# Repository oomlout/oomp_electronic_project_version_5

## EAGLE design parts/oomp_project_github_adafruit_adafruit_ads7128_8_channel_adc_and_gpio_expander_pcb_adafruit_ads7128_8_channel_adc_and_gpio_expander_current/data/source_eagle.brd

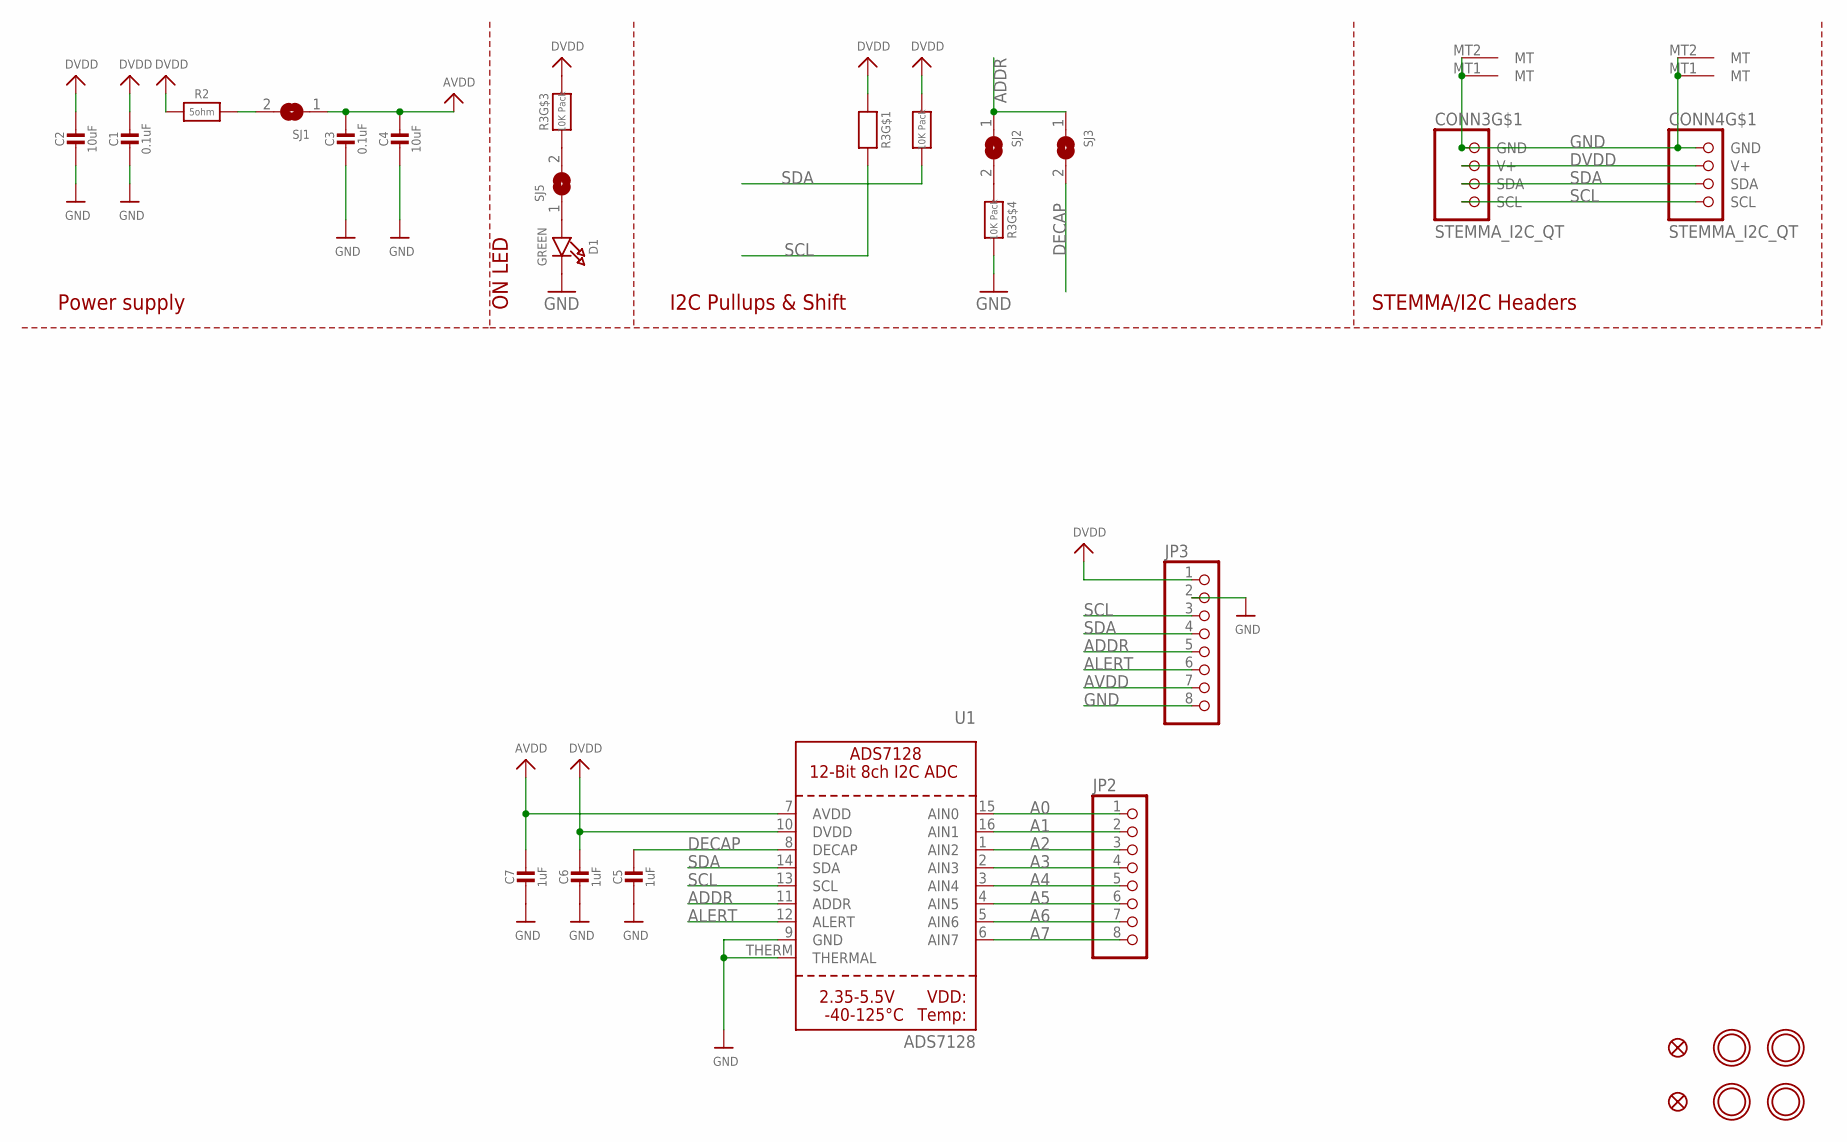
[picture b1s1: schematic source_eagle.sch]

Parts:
C1, C3: 0.1uF; 0603-NO
C2, C4: 10uF; 0805-NO
C5, C6, C7: 1uF; 0603-NO
CONN3, CONN4: STEMMA_I2C_QT; JST_SH4
D1: GREEN; CHIPLED_0603_NOOUTLINE
FID3, FID4: FIDUCIAL_0.5MM
JP2, JP3: HEADER-1X870MIL; 1X08_ROUND_70
R2: 5ohm; 0603-NO
R3: 10K Pack; RESPACK_4X0603
SJ1, SJ5: SOLDERJUMPERCLOSED; SOLDERJUMPER_CLOSEDWIRE
SJ2, SJ3: SOLDERJUMPER; SOLDERJUMPER_ARROW_NOPASTE
U1: ADS7128; WQFN16
U$1, U$17, U$19, U$21: MOUNTINGHOLE2.5; MOUNTINGHOLE_2.5_PLATED

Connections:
A0: JP2.1, U1.15 (AIN0)
A1: JP2.2, U1.16 (AIN1)
A2: JP2.3, U1.1 (AIN2)
A3: JP2.4, U1.2 (AIN3)
A4: JP2.5, U1.3 (AIN4)
A5: JP2.6, U1.4 (AIN5)
A6: JP2.7, U1.5 (AIN6)
A7: JP2.8, U1.6 (AIN7)
ADDR: JP3.5, SJ2.1, SJ3.1, U1.11 (ADDR)
ALERT: JP3.6, U1.12 (ALERT)
AVDD: C3.1, C4.1, C7.1, JP3.7, SJ1.1, U1.7 (AVDD)
DECAP: C5.1, SJ3.2, U1.8 (DECAP)
DVDD: C1.1, C2.1, C6.1, CONN3.2 (V+), CONN4.2 (V+), JP3.1, R2.1, R3.1, R3.2 (1), R3.6 (2), U1.10 (DVDD)
GND: C1.2, C2.2, C3.2, C4.2, C5.2, C6.2, C7.2, CONN3.1 (GND), CONN3.MT1 (MT), CONN3.MT2 (MT), CONN4.1 (GND), CONN4.MT1 (MT), CONN4.MT2 (MT), D1.C, JP3.2, JP3.8, R3.5 (2), U1.9 (GND), U1.THERM (THERMAL)
unnamed: D1.A, SJ5.1
unnamed: R3.3 (1), SJ5.2
unnamed: R2.2, SJ1.2
unnamed: R3.4 (1), SJ2.2
SCL: CONN3.4 (SCL), CONN4.4 (SCL), JP3.3, R3.8 (2), U1.13 (SCL)
SDA: CONN3.3 (SDA), CONN4.3 (SDA), JP3.4, R3.7 (2), U1.14 (SDA)

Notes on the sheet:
I2C Pullups & Shift
STEMMA/I2C Headers
ON LED
Power supply

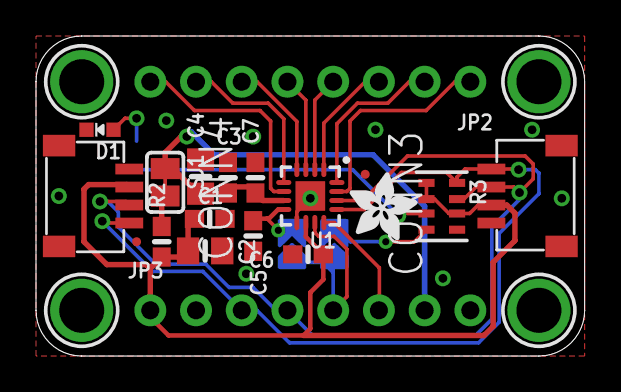
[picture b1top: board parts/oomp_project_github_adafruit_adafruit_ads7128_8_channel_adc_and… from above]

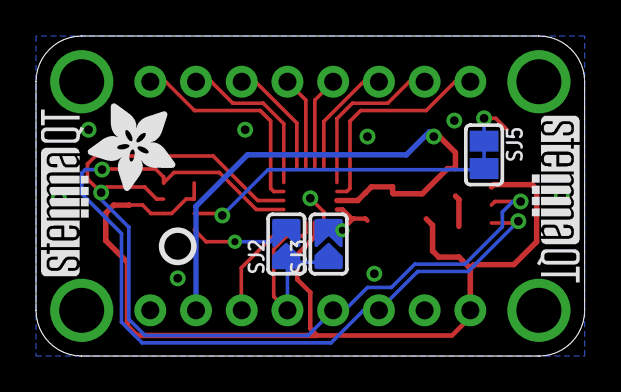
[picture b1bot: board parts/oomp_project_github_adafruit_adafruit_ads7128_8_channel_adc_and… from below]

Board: 2 copper layers, 30.5 x 17.8 mm, 58 parts (14 on the bottom side), 20 nets.

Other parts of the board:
PLABEL0: PLABEL0
PLABEL2: PLABEL2
PLABEL3: PLABEL3
PLABEL4: PLABEL4
PLABEL7: PLABEL7
PLABEL10: PLABEL10
PLABEL11: PLABEL11
PLABEL12: PLABEL12
PLABEL13: PLABEL13
PLABEL14: PLABEL14
PLABEL15: PLABEL15
PLABEL16: PLABEL16
PLABEL17: PLABEL17
PLABEL20: PLABEL20
PLABEL25: PLABEL25
PLABEL26: PLABEL26
PLABEL27: PLABEL27
PLABEL28: PLABEL28
PLABEL29: PLABEL29
PLABEL30: PLABEL30
PLABEL31: PLABEL31
PLABEL32: PLABEL32
PLABEL33: PLABEL33
PLABEL34: PLABEL34
PLABEL35: PLABEL35
PLABEL36: PLABEL36
PLABEL37: PLABEL37
PLABEL38: PLABEL38
U$22: ADAFRUIT_3.5MM
U$25: PCBFEAT-REV-040
U$27: ADAFRUIT_5MM
U$30, U$31: STEMMAQT

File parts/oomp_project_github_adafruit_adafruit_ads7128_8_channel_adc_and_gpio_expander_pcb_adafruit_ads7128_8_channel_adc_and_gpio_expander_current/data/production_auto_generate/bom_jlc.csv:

Comment,Designator,Footprint,LCSC Part #
,"JP2,JP3",1X08_ROUND_70,C492421
,U$22,ADAFRUIT_3.5MM,
,U$27,ADAFRUIT_5MM,
,U$25,PCBFEAT-REV-040,
,PLABEL0,PLABEL0,
,PLABEL10,PLABEL10,
,PLABEL11,PLABEL11,
,PLABEL12,PLABEL12,
,PLABEL13,PLABEL13,
,PLABEL14,PLABEL14,
,PLABEL15,PLABEL15,
,PLABEL16,PLABEL16,
,PLABEL17,PLABEL17,
,PLABEL2,PLABEL2,
,PLABEL20,PLABEL20,
,PLABEL25,PLABEL25,
,PLABEL26,PLABEL26,
,PLABEL27,PLABEL27,
,PLABEL28,PLABEL28,
,PLABEL29,PLABEL29,
,PLABEL3,PLABEL3,
,PLABEL30,PLABEL30,
,PLABEL31,PLABEL31,
,PLABEL32,PLABEL32,
,PLABEL33,PLABEL33,
,PLABEL34,PLABEL34,
,PLABEL35,PLABEL35,
,PLABEL36,PLABEL36,
,PLABEL37,PLABEL37,
,PLABEL38,PLABEL38,
,PLABEL4,PLABEL4,
,PLABEL7,PLABEL7,
,"U$30,U$31",STEMMAQT,
0.1uF,"C1,C3",0603-NO,C14663
10K Pack,R3,RESPACK_4X0603,C98220
10uF,"C2,C4",0805-NO,
1uF,"C5,C6,C7",0603-NO,C5673
5ohm,R2,0603-NO,
ADS7128,U1,WQFN16,
GREEN,D1,CHIPLED_0603_NOOUTLINE,
STEMMA_I2C_QT,"CONN3,CONN4",JST_SH4,C160404

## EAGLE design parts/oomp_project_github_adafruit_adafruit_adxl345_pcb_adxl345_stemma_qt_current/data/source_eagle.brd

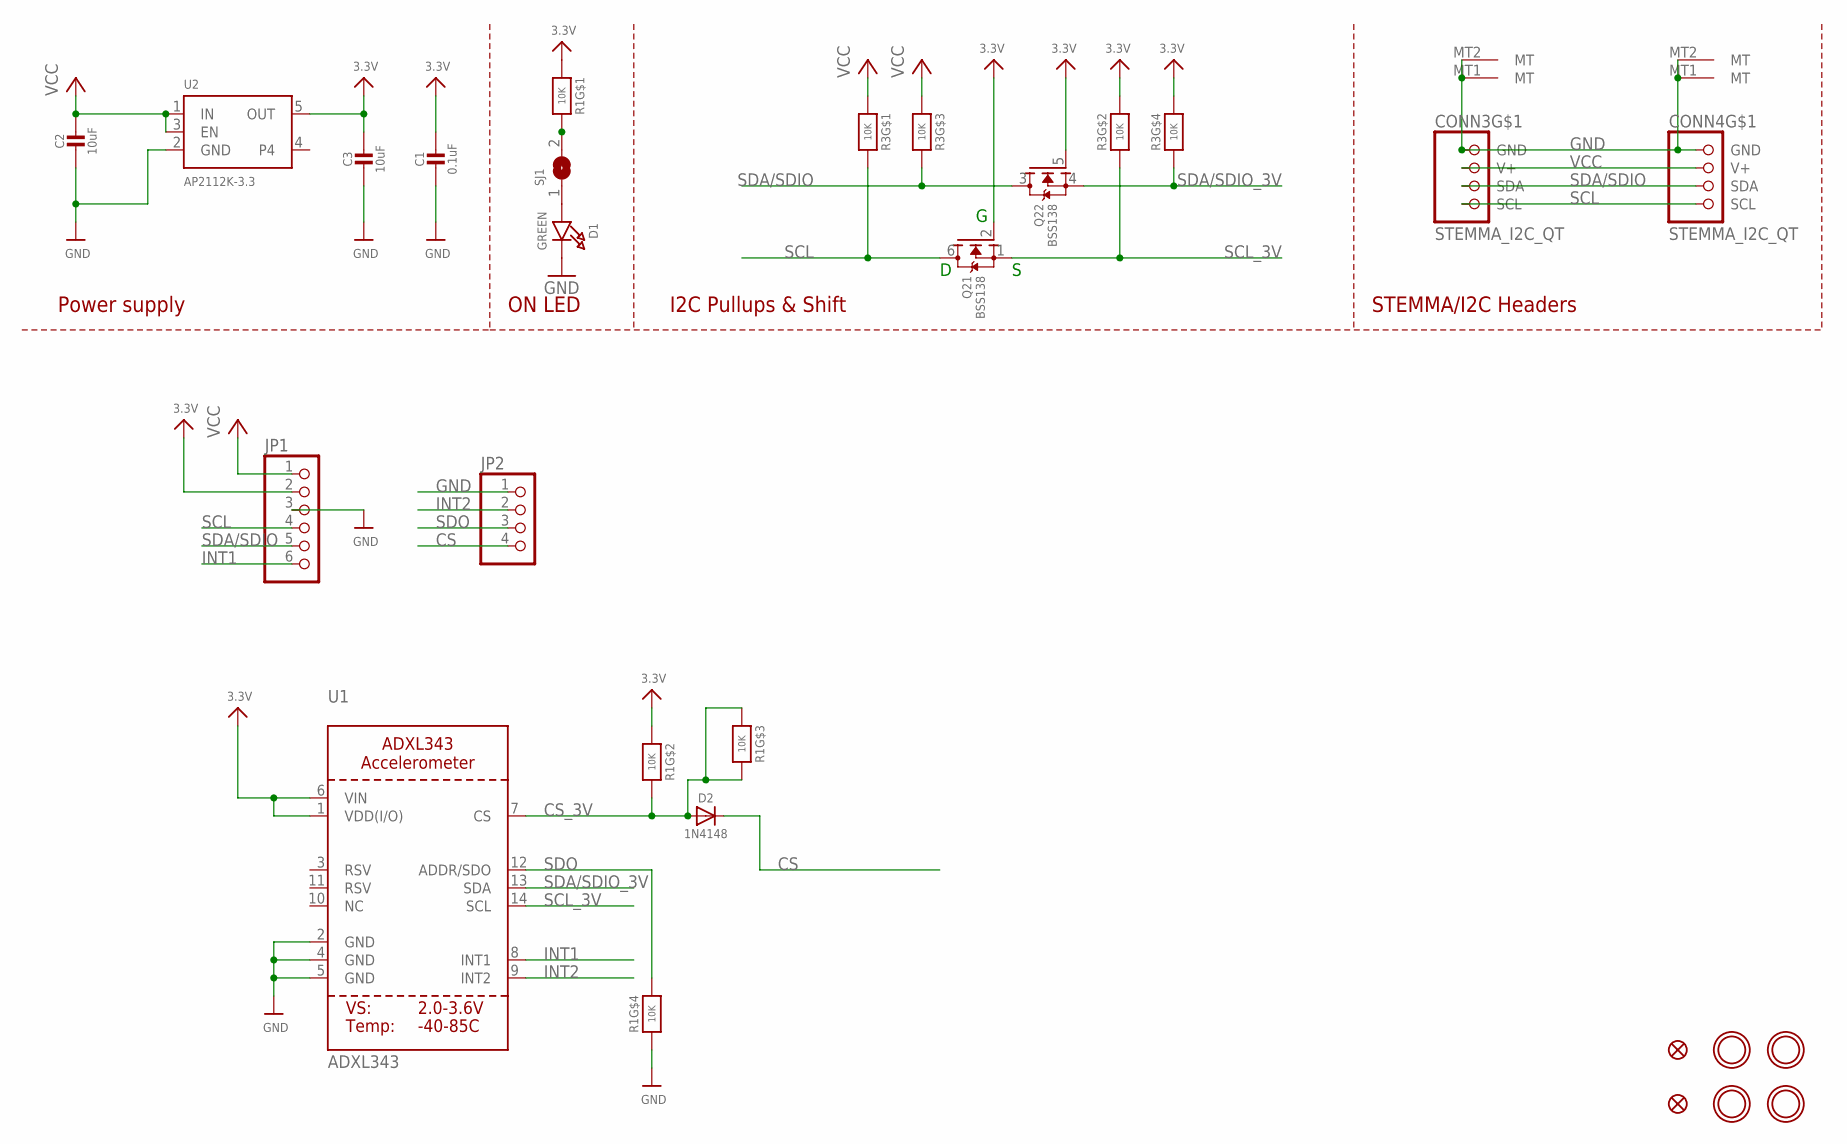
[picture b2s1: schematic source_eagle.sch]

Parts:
C1: 0.1uF; 0603-NO
C2: 10uF; _0805MP
C3: 10uF; 0805-NO
CONN3, CONN4: STEMMA_I2C_QT; JST_SH4
D1: GREEN; CHIPLED_0603_NOOUTLINE
D2: 1N4148; SOD-323
FID3, FID4: FIDUCIAL_1MM
JP1: HEADER-1X670MIL; 1X06_ROUND_70
JP2: HEADER-1X4ROUND; 1X04_ROUND
Q2: BSS138; SOT363
R1, R3: 10K; RESPACK_4X0603
SJ1: SOLDERJUMPERCLOSED; SOLDERJUMPER_CLOSEDWIRE
U1: ADXL343; LGA14
U2: AP2112K-3.3; SOT23-5
U$1, U$17, U$19, U$21: MOUNTINGHOLE2.5; MOUNTINGHOLE_2.5_PLATED

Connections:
3.3V: C1.1, C3.1, JP1.2, Q2.2 (G), Q2.5 (G), R1.1, R1.2 (1), R3.2 (1), R3.4 (1), U1.1 (VDD(I/O)), U1.6 (VIN), U2.5 (OUT)
CS: D2.C, JP2.4
CS_3V: D2.A, R1.3 (1), R1.6 (2), R1.7 (2), U1.7 (CS)
GND: C1.2, C2.2, C3.2, CONN3.1 (GND), CONN3.MT1 (MT), CONN3.MT2 (MT), CONN4.1 (GND), CONN4.MT1 (MT), CONN4.MT2 (MT), D1.C, JP1.3, JP2.1, R1.4 (1), U1.2 (GND), U1.4 (GND), U1.5 (GND), U2.2 (GND)
INT1: JP1.6, U1.8 (INT1)
INT2: JP2.2, U1.9 (INT2)
unnamed: R1.8 (2), SJ1.2
unnamed: D1.A, SJ1.1
SCL: CONN3.4 (SCL), CONN4.4 (SCL), JP1.4, Q2.6 (D), R3.8 (2)
SCL_3V: Q2.1 (S), R3.7 (2), U1.14 (SCL)
SDA/SDIO: CONN3.3 (SDA), CONN4.3 (SDA), JP1.5, Q2.3 (D), R3.6 (2)
SDA/SDIO_3V: Q2.4 (S), R3.5 (2), U1.13 (SDA)
SDO: JP2.3, R1.5 (2), U1.12 (ADDR/SDO)
VCC: C2.1, CONN3.2 (V+), CONN4.2 (V+), JP1.1, R3.1, R3.3 (1), U2.1 (IN), U2.3 (EN)

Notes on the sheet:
I2C Pullups & Shift
STEMMA/I2C Headers
ON LED
Power supply

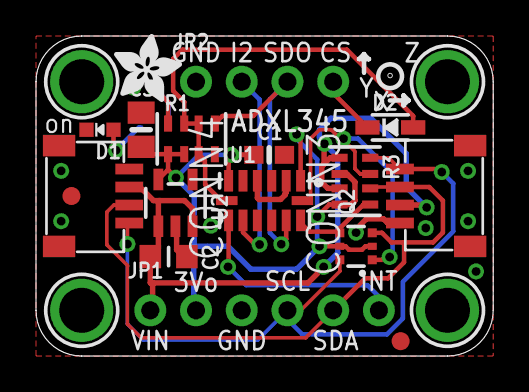
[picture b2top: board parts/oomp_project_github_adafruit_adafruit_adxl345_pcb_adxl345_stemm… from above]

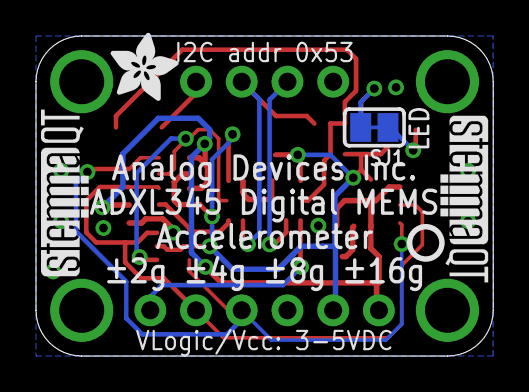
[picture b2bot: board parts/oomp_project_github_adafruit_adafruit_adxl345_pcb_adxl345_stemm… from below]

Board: 2 copper layers, 25.4 x 17.8 mm, 26 parts (5 on the bottom side), 14 nets.

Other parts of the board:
U$4, U$11: ADAFRUIT_3.5MM
U$25: PCBFEAT-REV-040
U$30, U$31: STEMMAQT

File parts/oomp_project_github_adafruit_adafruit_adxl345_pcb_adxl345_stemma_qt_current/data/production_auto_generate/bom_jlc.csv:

Comment,Designator,Footprint,LCSC Part #
,JP2,ADXL345 STEMMA QT-import-fps:1X04_ROUND,C42431795
,JP1,ADXL345 STEMMA QT-import-fps:1X06_ROUND_70,C37208
,"U$4,U$11",ADXL345 STEMMA QT-import-fps:ADAFRUIT_3.5MM,
,U$25,ADXL345 STEMMA QT-import-fps:PCBFEAT-REV-040,
,"U$30,U$31",ADXL345 STEMMA QT-import-fps:STEMMAQT,
0.1uF,C1,ADXL345 STEMMA QT-import-fps:0603-NO,C14663
10K,"R1,R3",ADXL345 STEMMA QT-import-fps:RESPACK_4X0603,C98220
10uF,C3,ADXL345 STEMMA QT-import-fps:0805-NO,
10uF,C2,ADXL345 STEMMA QT-import-fps:_0805MP,
1N4148,D2,ADXL345 STEMMA QT-import-fps:SOD-323,
ADXL343,U1,ADXL345 STEMMA QT-import-fps:LGA14,
AP2112K-3.3,U2,ADXL345 STEMMA QT-import-fps:SOT23-5,
BSS138,Q2,ADXL345 STEMMA QT-import-fps:SOT363,
GREEN,D1,ADXL345 STEMMA QT-import-fps:CHIPLED_0603_NOOUTLINE,
STEMMA_I2C_QT,"CONN3,CONN4",ADXL345 STEMMA QT-import-fps:JST_SH4,C160404

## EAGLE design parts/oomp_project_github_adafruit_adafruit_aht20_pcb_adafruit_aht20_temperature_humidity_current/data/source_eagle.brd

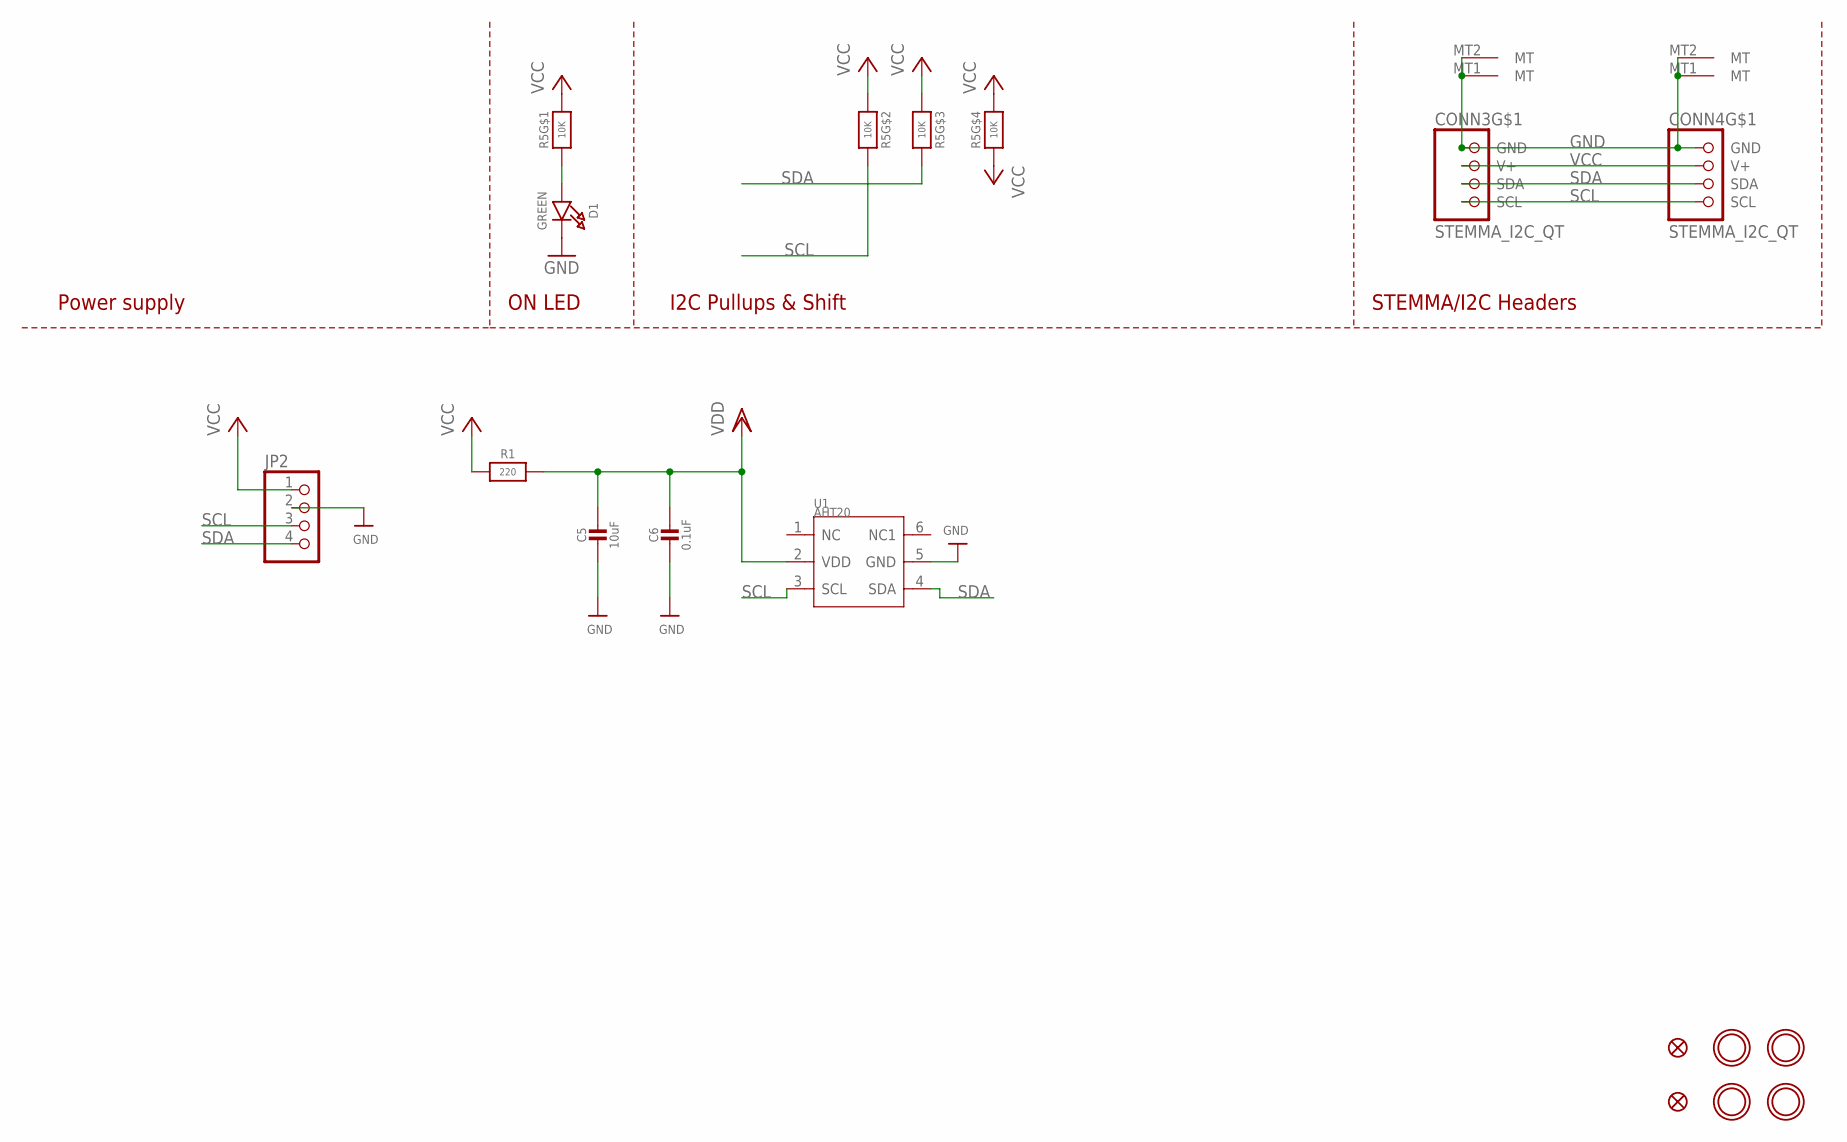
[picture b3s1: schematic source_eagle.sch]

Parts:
C5: 10uF; 0805-NO
C6: 0.1uF; 0603-NO
CONN3, CONN4: STEMMA_I2C_QT; JST_SH4
D1: GREEN; CHIPLED_0603_NOOUTLINE
FID3, FID4: FIDUCIAL_1MM
JP2: HEADER-1X476MIL; 1X04_ROUND_76
R1: 220; 0603-NO
R5: 10K; RESPACK_4X0603
U1: AHT20; SNR6-1.0-3X3X1MM
U$19, U$20, U$22, U$25: MOUNTINGHOLE2.5; MOUNTINGHOLE_2.5_PLATED

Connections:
GND: C5.2, C6.2, CONN3.1 (GND), CONN3.MT1 (MT), CONN3.MT2 (MT), CONN4.1 (GND), CONN4.MT1 (MT), CONN4.MT2 (MT), D1.C, JP2.2, U1.5 (GND)
unnamed: D1.A, R5.1
SCL: CONN3.4 (SCL), CONN4.4 (SCL), JP2.3, R5.7 (2), U1.3 (SCL)
SDA: CONN3.3 (SDA), CONN4.3 (SDA), JP2.4, R5.6 (2), U1.4 (SDA)
VCC: CONN3.2 (V+), CONN4.2 (V+), JP2.1, R1.1, R5.2 (1), R5.3 (1), R5.4 (1), R5.5 (2), R5.8 (2)
VDD: C5.1, C6.1, R1.2, U1.2 (VDD)

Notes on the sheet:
I2C Pullups & Shift
STEMMA/I2C Headers
ON LED
Power supply

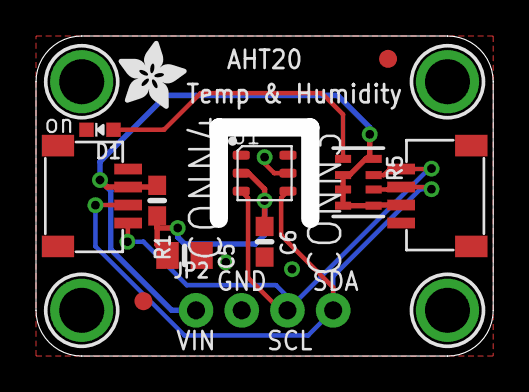
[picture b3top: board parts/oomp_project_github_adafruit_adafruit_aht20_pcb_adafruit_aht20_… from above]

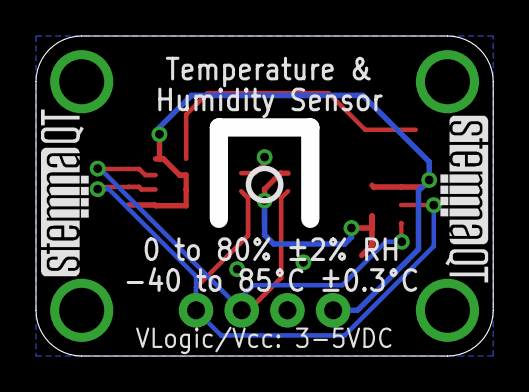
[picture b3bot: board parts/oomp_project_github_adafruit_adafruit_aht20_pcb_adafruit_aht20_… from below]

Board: 2 copper layers, 25.4 x 17.8 mm, 19 parts (3 on the bottom side), 6 nets.

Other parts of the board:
U$28: ADAFRUIT_3.5MM
U$29: PCBFEAT-REV-040
U$30, U$31: STEMMAQT

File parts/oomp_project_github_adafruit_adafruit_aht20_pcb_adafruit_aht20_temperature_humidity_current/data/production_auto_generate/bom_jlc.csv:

Comment,Designator,Footprint,LCSC Part #
,JP2,Adafruit AHT20 Temperature & Humidity-import-fps:1X04_ROUND_76,C42431795
,U$28,Adafruit AHT20 Temperature & Humidity-import-fps:ADAFRUIT_3.5MM,
,U$29,Adafruit AHT20 Temperature & Humidity-import-fps:PCBFEAT-REV-040,
,"U$30,U$31",Adafruit AHT20 Temperature & Humidity-import-fps:STEMMAQT,
0.1uF,C6,Adafruit AHT20 Temperature & Humidity-import-fps:0603-NO,C14663
10K,R5,Adafruit AHT20 Temperature & Humidity-import-fps:RESPACK_4X0603,C98220
10uF,C5,Adafruit AHT20 Temperature & Humidity-import-fps:0805-NO,
220,R1,Adafruit AHT20 Temperature & Humidity-import-fps:0603-NO,C2907127
AHT20,U1,Adafruit AHT20 Temperature & Humidity-import-fps:SNR6-1.0-3X3X1MM,
GREEN,D1,Adafruit AHT20 Temperature & Humidity-import-fps:CHIPLED_0603_NOOUTLINE,
STEMMA_I2C_QT,"CONN3,CONN4",Adafruit AHT20 Temperature & Humidity-import-fps:JST_SH4,C160404

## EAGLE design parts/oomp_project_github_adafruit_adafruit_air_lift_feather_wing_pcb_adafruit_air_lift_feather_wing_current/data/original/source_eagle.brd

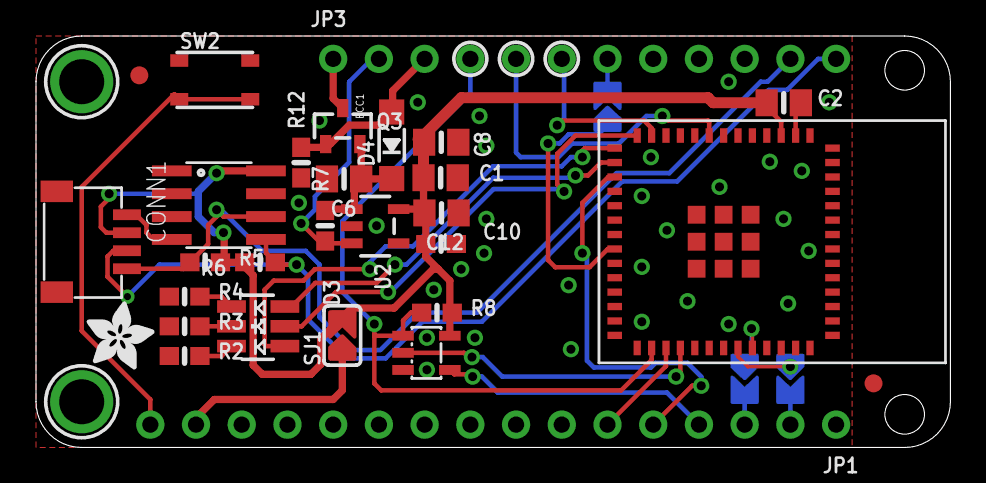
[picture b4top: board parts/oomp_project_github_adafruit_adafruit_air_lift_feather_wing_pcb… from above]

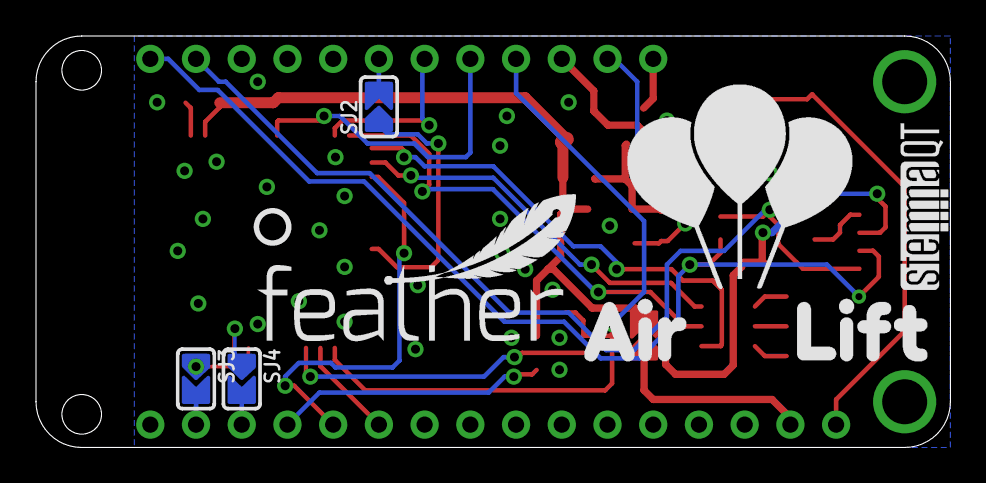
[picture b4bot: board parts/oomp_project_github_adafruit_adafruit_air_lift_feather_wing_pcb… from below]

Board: 2 copper layers, 50.8 x 22.9 mm, 73 parts (21 on the bottom side), 29 nets.

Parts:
C1, C2, C6, C8, C10: 10uF; 0805-NO
C12: 0.1uF; 0603-NO
CONN1: STEMMA_I2C_QT; JST_SH4
D3: RGB; RGBLED_3535_PLCC6
D4: MBR0520; SOD-123
ECC1: ATECCx08; SOIC8
IC2: 74AHC1G125; SOT23-5L
JP1: 1X16_ROUND_MIN
JP3: 1X12_ROUND_MIN
PLABEL0: PLABEL0
PLABEL1: PLABEL1
PLABEL2: PLABEL2
PLABEL3: PLABEL3
PLABEL4: PLABEL4
PLABEL5: PLABEL5
PLABEL6: PLABEL6
PLABEL7: PLABEL7
PLABEL8: PLABEL8
PLABEL9: PLABEL9
PLABEL10: PLABEL10
PLABEL11: PLABEL11
PLABEL12: PLABEL12
PLABEL13: PLABEL13
PLABEL14: PLABEL14
PLABEL15: PLABEL15
PLABEL16: PLABEL16
PLABEL17: PLABEL17
PLABEL18: PLABEL18
PLABEL19: PLABEL19
PLABEL20: PLABEL20
PLABEL21: PLABEL21
PLABEL22: PLABEL22
PLABEL23: PLABEL23
PLABEL24: PLABEL24
PLABEL25: PLABEL25
PLABEL26: PLABEL26
PLABEL27: PLABEL27
PLABEL28: PLABEL28
PLABEL29: PLABEL29
PLABEL30: PLABEL30
PLABEL31: PLABEL31
PLABEL32: PLABEL32
PLABEL33: PLABEL33
PLABEL34: PLABEL34
Q3: AO3401; SOT23-R
R2, R3, R4: 1K; 0603-NO
R5, R6, R8: 10K; 0603-NO
R7, R12: 100K; 0603-NO
SJ1: JUMPER; SOLDERJUMPER_ARROW_NOPASTE
SJ2, SJ3, SJ4: SOLDERJUMPER_ARROW_NOPASTE
SW2: RKB2; BTN_RKB2_4.6X2.8
U2: RT9080-3.3; SOT23-5
U$6: AIRLIFT
U$7: FEATHERLOGO_MED
U$12: STEMMAQT
U$13: PCBFEAT-REV-040
U$15: ADAFRUIT_3.5MM
U$31, U$32: MOUNTINGHOLE2.5; MOUNTINGHOLE_2.5_PLATED
U$34, U$35: FIDUCIAL_1MM
X1: ESP32-MINI-1

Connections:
3.3V: C1.1, C2.1, C8.1, C10.1, C12.1, CONN1.2, ECC1.8, IC2.5, R5.2, R6.2, R8.2, SJ1.2, U2.5, X1.3
BLUE: D3.6, X1.15
EN: JP3.2, R7.1, U2.3
ESP_BUSY: JP3.6, X1.12
ESP_CS: IC2.1, JP3.4, R8.1, X1.29
ESP_GPIO0: SJ2.1, X1.21
ESP_MISO: IC2.2, X1.31
ESP_RESET: JP3.5, X1.8
ESP_RX: SJ3.1, X1.35
ESP_TX: SJ4.1, X1.36
GND: C1.2, C2.2, C6.2, C8.2, C10.2, C12.2, CONN1.1, CONN1.MT1, CONN1.MT2, ECC1.4, IC2.3, JP1.13, R2.1, R3.1, R4.1, R12.1, SW2.A, SW2.A', U2.2, X1.1, X1.2, X1.27, X1.38, X1.39, X1.40, X1.41, X1.42, X1.43, X1.44, X1.45, X1.46, X1.47, X1.48, X1.49, X1.50, X1.51, X1.52, X1.53, X1.54, X1.55, X1.56, X1.57, X1.58, X1.59, X1.60, X1.61, X1.62, X1.63
GREEN: D3.5, X1.13
MISO: IC2.4, JP1.4
MOSI: JP1.5, X1.16
unnamed: JP1.15, SJ1.1
unnamed: D3.3, R2.2
unnamed: D3.2, R3.2
unnamed: D3.1, R4.2
unnamed: JP3.7, SJ2.2
unnamed: JP1.2, SJ3.2
unnamed: C6.1, D4.C, Q3.2, R7.2, U2.1
unnamed: JP1.3, SJ4.2
RED: D3.4, X1.14
RESET: JP1.16, SW2.B, SW2.B'
SCK: JP1.6, X1.30
SCL: CONN1.4, ECC1.6, JP3.11, R5.1
SDA: CONN1.3, ECC1.5, JP3.12, R6.1
VBAT: JP3.1, Q3.3
VBUS: D4.A, JP3.3, Q3.1, R12.2

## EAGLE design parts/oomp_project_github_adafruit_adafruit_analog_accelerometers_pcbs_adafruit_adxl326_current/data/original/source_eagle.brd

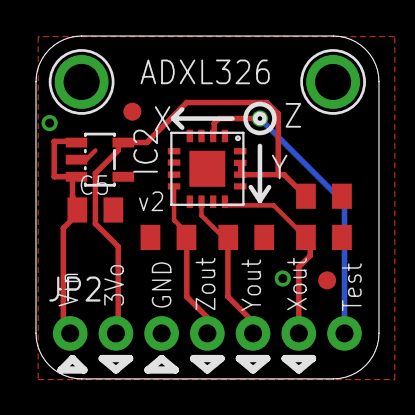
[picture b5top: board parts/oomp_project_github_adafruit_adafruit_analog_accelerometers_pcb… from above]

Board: 2 copper layers, 19.1 x 19.1 mm, 13 parts (1 on the bottom side), 7 nets.

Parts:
C1, C5: 10uF; C0805K
C2, C3, C4: 0.1uF; C0805K
IC1: ADXL33X; 16LCSP
IC2: LP298XS; SOT23-5L
JP2: 1X07_ROUND_76
U$1, U$2: FIDUCIAL; FIDUCIAL_1MM
U$4: ADAFRUIT_2.5MM
U$5, U$8: MOUNTINGHOLE2.0; MOUNTINGHOLE_2.0_PLATED

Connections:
+3V3: C1.1, IC1.14, IC1.15, IC2.5, JP2.2
+5V: C5.1, IC2.1, IC2.3, JP2.1
GND: C1.2, C2.2, C3.2, C4.2, C5.2, IC1.3, IC1.5, IC1.6, IC1.7, IC2.2, JP2.3
ST: IC1.2, JP2.7
XOUT: C4.1, IC1.12, JP2.6
YOUT: C3.1, IC1.10, JP2.5
ZOUT: C2.1, IC1.8, JP2.4

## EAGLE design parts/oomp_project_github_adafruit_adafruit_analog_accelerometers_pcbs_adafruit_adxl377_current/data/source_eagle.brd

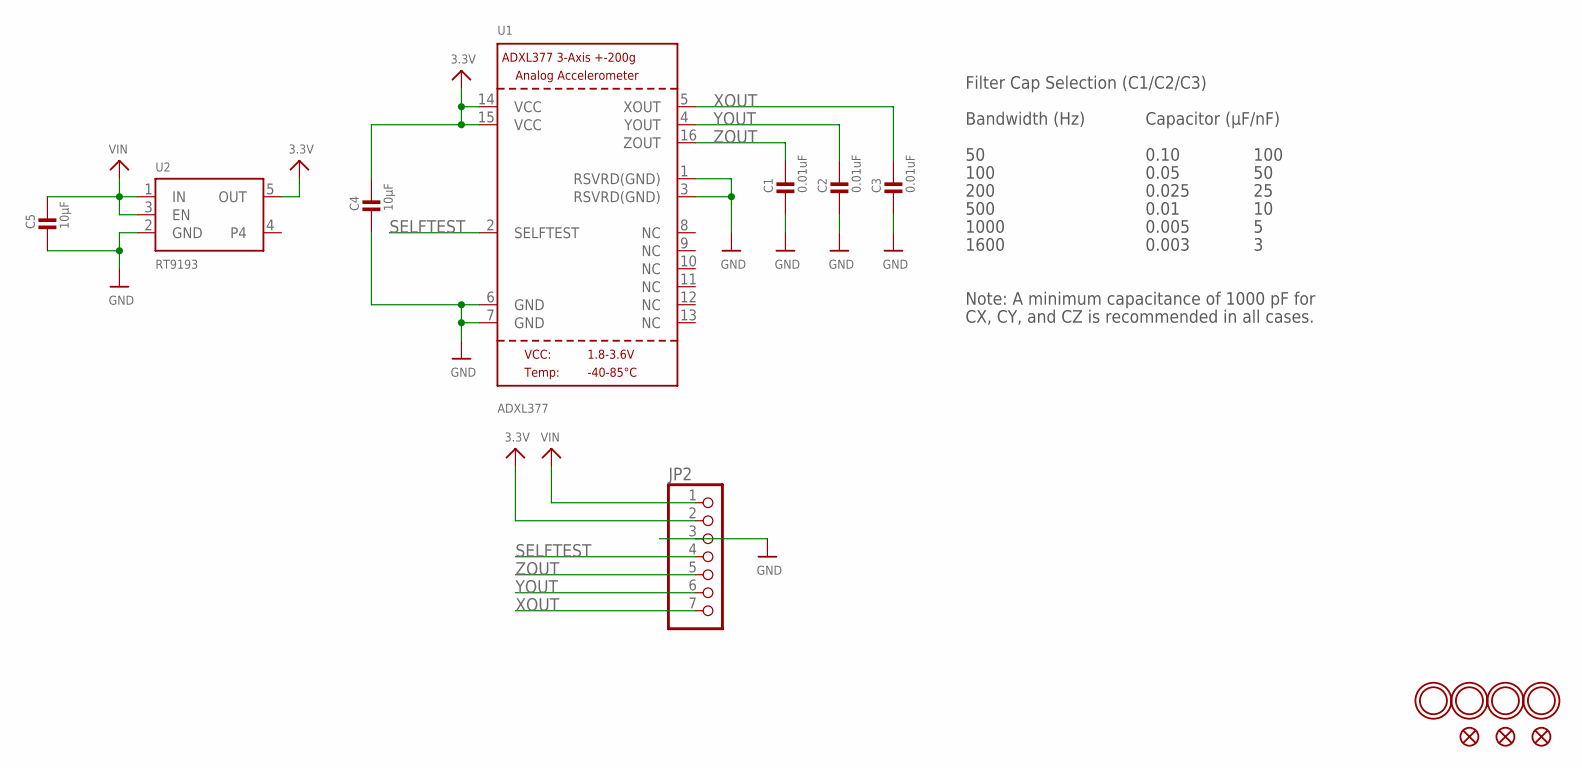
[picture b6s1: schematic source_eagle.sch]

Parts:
C1, C2, C3: 0.01uF; _0805
C4, C5: 10µF; _0805
FID1, FID2, FID3: FIDUCIAL""; FIDUCIAL_1MM
JP2: HEADER-1X770MIL; 1X07_ROUND_70
U1: ADXL377; LFCSP16_LQ
U2: RT9193; SOT23-5
U$2, U$3, U$17, U$18: MOUNTINGHOLE2.5; MOUNTINGHOLE_2.5_PLATED

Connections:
3.3V: C4.1, JP2.2, U1.14 (VCC), U1.15 (VCC), U2.5 (OUT)
GND: C1.2, C2.2, C3.2, C4.2, C5.2, JP2.3, U1.1 (RSVRD(GND)), U1.3 (RSVRD(GND)), U1.6 (GND), U1.7 (GND), U2.2 (GND)
SELFTEST: JP2.4, U1.2 (SELFTEST)
VIN: C5.1, JP2.1, U2.1 (IN), U2.3 (EN)
XOUT: C3.1, JP2.7, U1.5 (XOUT)
YOUT: C2.1, JP2.6, U1.4 (YOUT)
ZOUT: C1.1, JP2.5, U1.16 (ZOUT)

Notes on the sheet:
Filter Cap Selection (C1/C2/C3)
Bandwidth (Hz)
Capacitor (µF/nF)
100
200
500
1000
1600
0.10
0.05
0.025
0.01
0.005
0.003
Note: A minimum capacitance of 1000 pF for
CX, CY, and CZ is recommended in all cases.

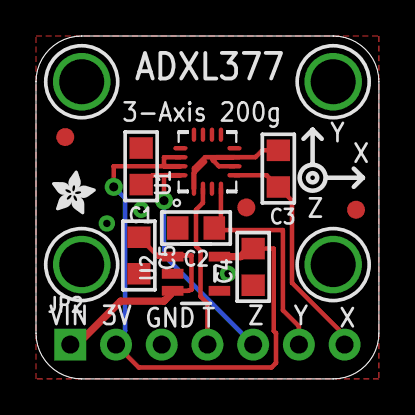
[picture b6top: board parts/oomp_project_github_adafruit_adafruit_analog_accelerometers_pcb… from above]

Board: 2 copper layers, 19.0 x 19.1 mm, 17 parts (1 on the bottom side), 7 nets.

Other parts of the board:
U$16, U$19: ADAFRUIT_2.5MM

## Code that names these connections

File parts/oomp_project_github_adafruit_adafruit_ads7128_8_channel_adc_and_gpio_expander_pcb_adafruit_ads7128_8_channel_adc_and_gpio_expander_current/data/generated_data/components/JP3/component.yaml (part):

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      connected_to:
      - reference: '#U$7'
        pin_number: '1'
        pin_name: DVDD
      - reference: '#U$8'
        pin_number: '1'
        pin_name: DVDD
      - reference: '#U$10'
        pin_number: '1'
        pin_name: DVDD
      - reference: '#U$16'
        pin_number: '1'
        pin_name: DVDD
      - reference: '#U$20'
        pin_number: '1'
        pin_name: DVDD
      - reference: '#U$23'
        pin_number: '1'
        pin_name: DVDD
      - reference: '#U$24'
        pin_number: '1'
        pin_name: DVDD
      - reference: '#U$26'
        pin_number: '1'
        pin_name: DVDD
      - reference: C1
        pin_number: '1'
        pin_name: '1'
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        pin_name: '1'
      - reference: U1
        pin_number: '10'
        pin_name: DVDD
    - number: '2'
      name: '2'
      electrical_type: passive
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      connected_to:
      - reference: U1
        pin_number: '12'
        pin_name: ALERT
    - number: '7'
      name: '7'
      electrical_type: passive
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      connected_to:
      - reference: '#U$9'
        pin_number: '1'
        pin_name: AVDD
      - reference: '#U$15'
        pin_number: '1'
        pin_name: AVDD
      - reference: C3
        pin_number: '1'
        pin_name: '1'
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        pin_name: '1'
      - reference: U1
        pin_number: '7'
        pin_name: AVDD
    - number: '8'
      name: '8'
      electrical_type: passive
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    pin_name: GND
  - reference: '#U$7'
    pin_number: '1'
    pin_name: DVDD
  - reference: '#U$8'
    pin_number: '1'
    pin_name: DVDD
  - reference: '#U$9'
    pin_number: '1'
    pin_name: AVDD
  - reference: '#U$10'
    pin_number: '1'
    pin_name: DVDD
  - reference: '#U$11'
    pin_number: '1'
    pin_name: GND
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    pin_name: GND
  - reference: '#U$15'
    pin_number: '1'
    pin_name: AVDD
  - reference: '#U$16'
    pin_number: '1'
    pin_name: DVDD
  - reference: '#U$20'
    pin_number: '1'
    pin_name: DVDD
  - reference: '#U$23'
    pin_number: '1'
    pin_name: DVDD
  - reference: '#U$24'
    pin_number: '1'
    pin_name: DVDD
  - reference: '#U$26'
    pin_number: '1'
    pin_name: DVDD
  - reference: C1
    pin_number: '1'
    pin_name: '1'
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    pin_name: '1'
  - reference: U1
    pin_number: '10'
    pin_name: DVDD
  - reference: U1
    pin_number: '11'
    pin_name: ADDR
  - reference: U1
    pin_number: '12'
    pin_name: ALERT
  - reference: U1
    pin_number: '13'
    pin_name: SCL
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    pin_name: SDA
  - reference: U1
    pin_number: '7'
    pin_name: AVDD
  - reference: U1
    pin_number: '9'
    pin_name: GND
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

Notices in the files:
parts and their libraries:
microbuilder: This work is placed in the public domain, and may be freely used for commercial and non-commercial work with the following conditions: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
